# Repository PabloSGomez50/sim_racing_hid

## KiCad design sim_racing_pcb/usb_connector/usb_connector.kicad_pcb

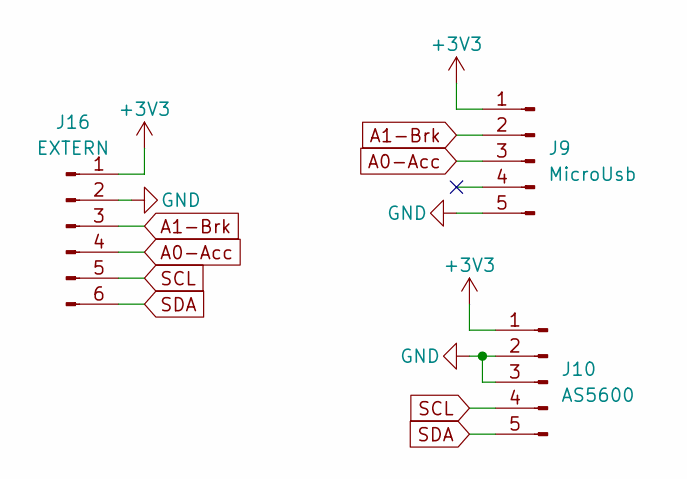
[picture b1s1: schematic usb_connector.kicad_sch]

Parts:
J9: MicroUsb; PinHeader_1x05_P2.54mm_Vertical
J10: AS5600; PinHeader_1x05_P2.54mm_Vertical
J16: EXTERN; Molex_KK-254_AE-6410-06A_1x06_P2.54mm_Vertical

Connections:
+3V3: J9.1, J10.1, J16.1
A0-Acc: J9.3, J16.4
A1-Brk: J9.2, J16.3
GND: J9.5, J10.2, J10.3, J16.2
SCL: J10.4, J16.5
SDA: J10.5, J16.6

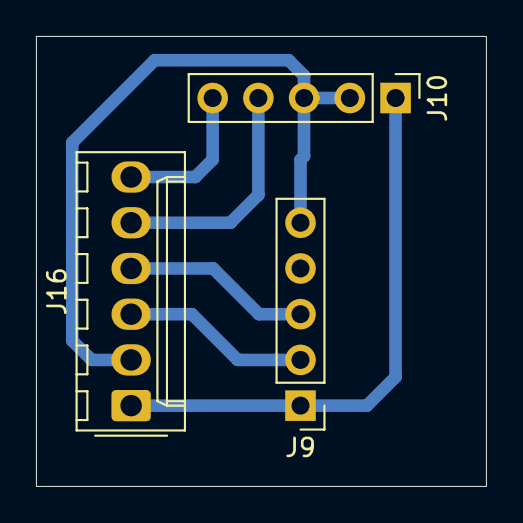
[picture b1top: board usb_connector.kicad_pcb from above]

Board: 2 copper layers, 25.0 x 25.0 mm, 3 parts (0 on the bottom side), 6 nets.

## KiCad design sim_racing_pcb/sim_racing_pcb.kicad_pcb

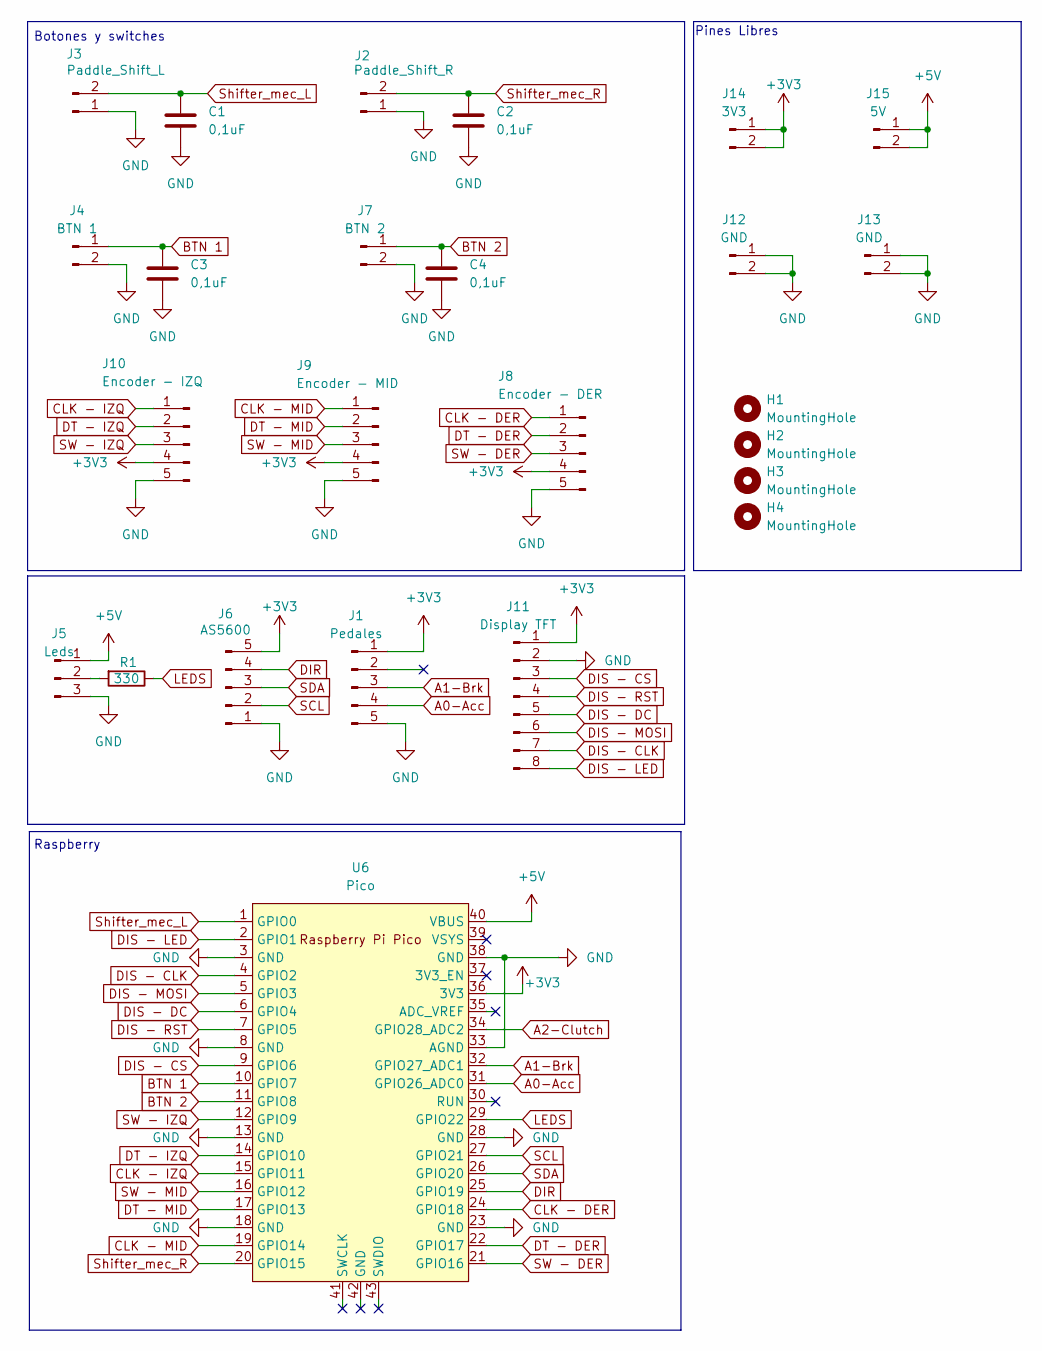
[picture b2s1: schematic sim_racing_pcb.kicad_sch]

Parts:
C1, C2, C3, C4: 0,1uF; C_Disc_D3.4mm_W2.1mm_P2.50mm
H1, H2, H3, H4: MountingHole; MountingHole_3.2mm_M3_DIN965
J1: Pedales; Molex_KK-254_AE-6410-05A_1x05_P2.54mm_Vertical
J2: Paddle_Shift_R; Molex_KK-254_AE-6410-02A_1x02_P2.54mm_Vertical
J3: Paddle_Shift_L; Molex_KK-254_AE-6410-02A_1x02_P2.54mm_Vertical
J4: BTN 1; Molex_KK-254_AE-6410-02A_1x02_P2.54mm_Vertical
J5: Leds; Molex_KK-254_AE-6410-03A_1x03_P2.54mm_Vertical
J6: AS5600; Molex_KK-254_AE-6410-05A_1x05_P2.54mm_Vertical
J7: BTN 2; Molex_KK-254_AE-6410-02A_1x02_P2.54mm_Vertical
J8: Encoder - DER; Molex_KK-254_AE-6410-05A_1x05_P2.54mm_Vertical
J9: Encoder - MID; Molex_KK-254_AE-6410-05A_1x05_P2.54mm_Vertical
J10: Encoder - IZQ; Molex_KK-254_AE-6410-05A_1x05_P2.54mm_Vertical
J11: Display TFT; Molex_KK-254_AE-6410-08A_1x08_P2.54mm_Vertical
J12, J13: GND; PinHeader_1x02_P2.54mm_Vertical
J14: 3V3; PinHeader_1x02_P2.54mm_Vertical
J15: 5V; PinHeader_1x02_P2.54mm_Vertical
R1: 330; R_Axial_DIN0207_L6.3mm_D2.5mm_P15.24mm_Horizontal
U6: Pico; RPi_Pico_SMD_TH

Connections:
+3V3: J1.1, J6.5, J8.4, J9.4, J10.4, J11.1, J14.1, J14.2, U6.36 (3V3); also elsewhere on the board
+5V: J5.1, J15.1, J15.2, U6.40 (VBUS)
A0-Acc: J1.4, U6.31 (GPIO26_ADC0); also elsewhere on the board
A1-Brk: J1.3, U6.32 (GPIO27_ADC1); also elsewhere on the board
A2-Clutch: U6.34 (GPIO28_ADC2)
BTN 1: C3.1, J4.1, U6.10 (GPIO7)
BTN 2: C4.1, J7.1, U6.11 (GPIO8)
CLK - DER: J8.1, U6.24 (GPIO18)
CLK - IZQ: J10.1, U6.15 (GPIO11)
CLK - MID: J9.1, U6.19 (GPIO14)
DIS - CLK: J11.7, U6.4 (GPIO2)
DIS - CS: J11.3, U6.9 (GPIO6)
DIS - DC: J11.5, U6.6 (GPIO4)
DIS - LED: J11.8, U6.2 (GPIO1)
DIS - MOSI: J11.6, U6.5 (GPIO3)
DIS - RST: J11.4, U6.7 (GPIO5)
DT - DER: J8.2, U6.22 (GPIO17)
DT - IZQ: J10.2, U6.14 (GPIO10)
DT - MID: J9.2, U6.17 (GPIO13)
LEDS: R1.1, U6.29 (GPIO22)
unnamed: J5.2, R1.2
SCL: J6.2, U6.27 (GPIO21); also elsewhere on the board
SDA: J6.3, U6.26 (GPIO20); also elsewhere on the board
SW - DER: J8.3, U6.21 (GPIO16)
SW - IZQ: J10.3, U6.12 (GPIO9)
SW - MID: J9.3, U6.16 (GPIO12)
Shifter_mec_L: C1.1, J3.2, U6.1 (GPIO0)
Shifter_mec_R: C2.1, J2.2, U6.20 (GPIO15)

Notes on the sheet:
Botones y switches
Pines Libres
Raspberry

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
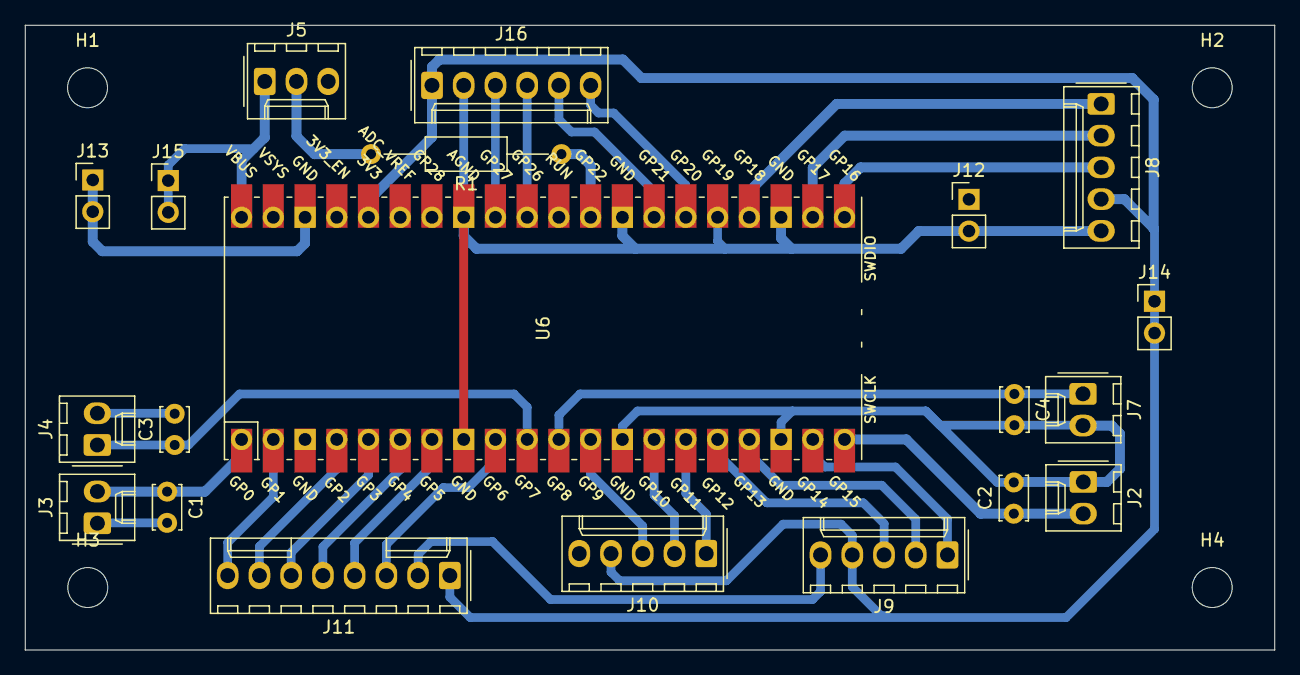
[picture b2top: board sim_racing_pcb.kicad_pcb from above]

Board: 2 copper layers, 100.0 x 50.0 mm, 24 parts (0 on the bottom side), 28 nets.

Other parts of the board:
J16: EXTERN; Molex_KK-254_AE-6410-06A_1x06_P2.54mm_Vertical

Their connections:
+3V3: J16.1; also elsewhere on the board
A0-Acc: J16.4; also elsewhere on the board
A1-Brk: J16.3; also elsewhere on the board
SCL: J16.5; also elsewhere on the board
SDA: J16.6; also elsewhere on the board

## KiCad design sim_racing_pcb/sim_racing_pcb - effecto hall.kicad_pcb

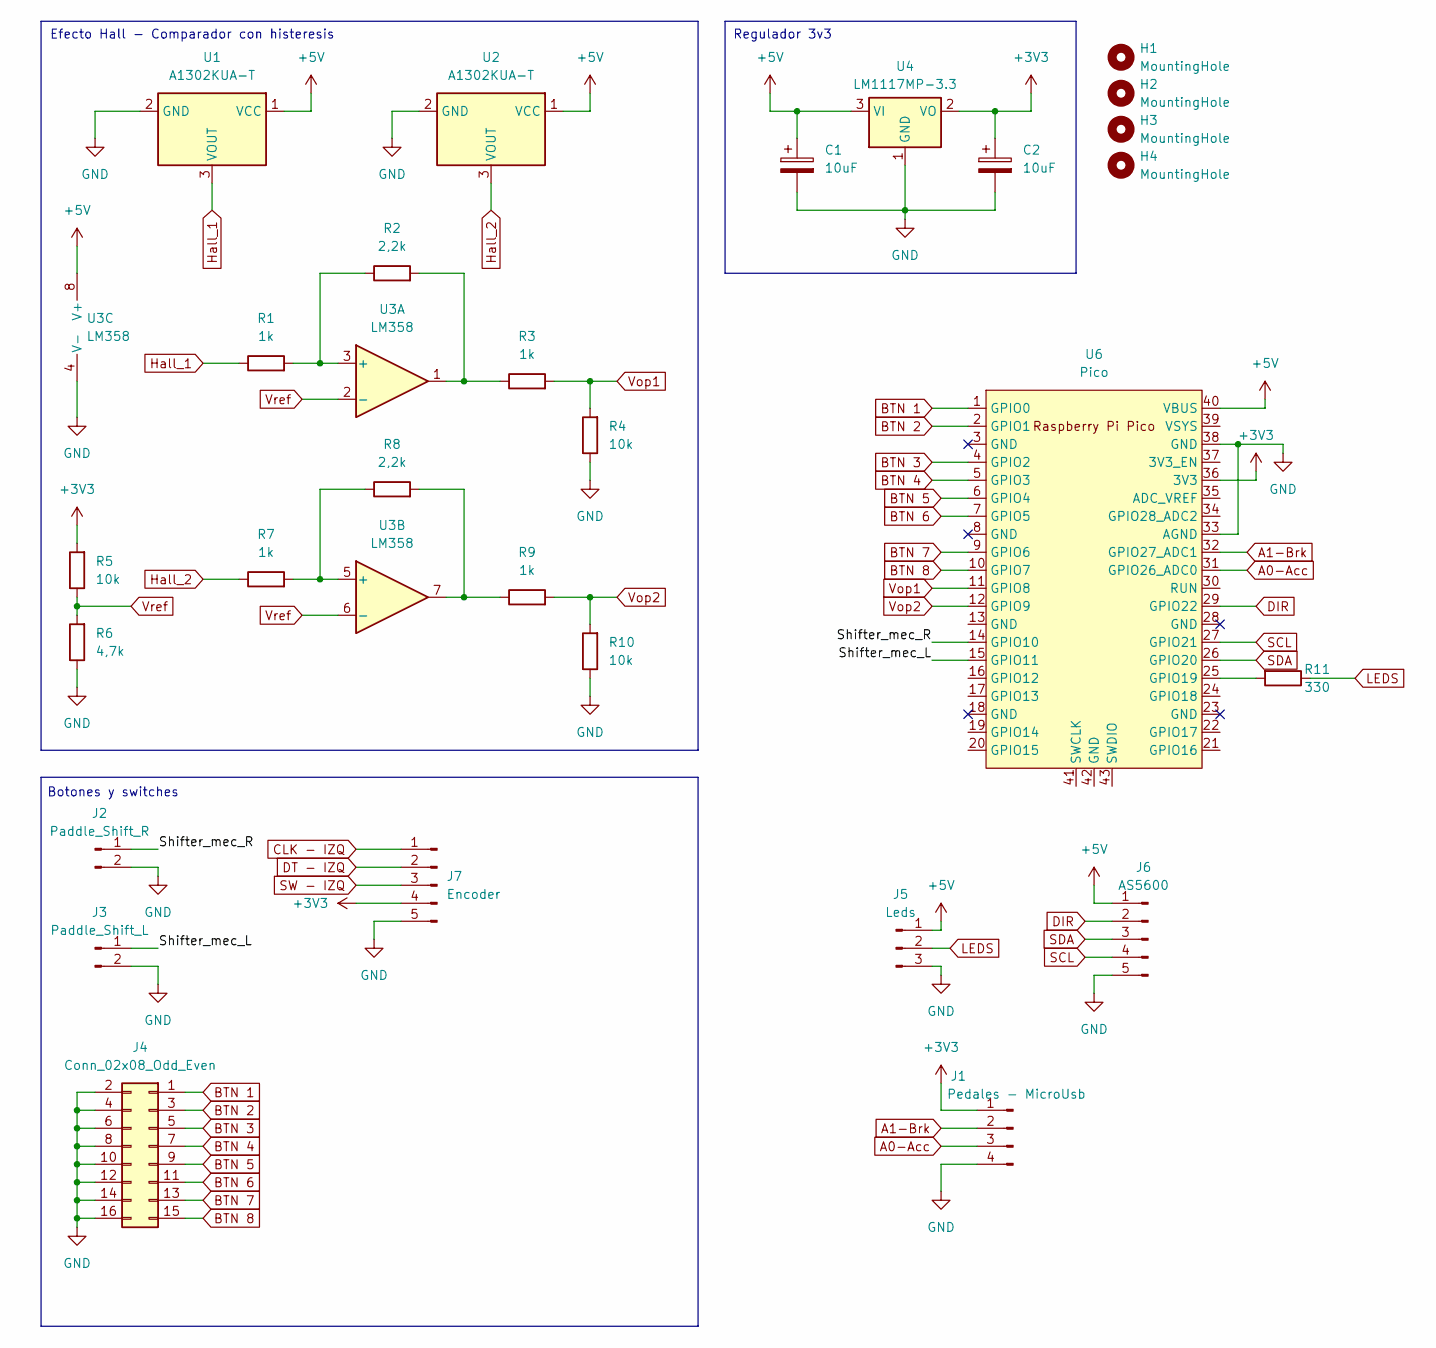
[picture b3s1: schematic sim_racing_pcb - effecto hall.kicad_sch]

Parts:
C1, C2: 10uF; CP_Radial_D5.0mm_P2.50mm
H1, H2, H3, H4: MountingHole; MountingHole_3.2mm_M3_DIN965
J1: Pedales - MicroUsb; PinHeader_1x04_P2.54mm_Vertical
J2: Paddle_Shift_R; PinHeader_1x02_P2.54mm_Vertical
J3: Paddle_Shift_L; PinHeader_1x02_P2.54mm_Vertical
J4: Conn_02x08_Odd_Even; PinHeader_2x08_P2.54mm_Vertical
J5: Leds; PinHeader_1x03_P2.54mm_Vertical
J6: AS5600; PinHeader_1x05_P2.54mm_Vertical
J7: Encoder; PinHeader_1x05_P2.54mm_Vertical
R1, R3, R7, R9: 1k; R_Axial_DIN0207_L6.3mm_D2.5mm_P10.16mm_Horizontal
R2, R8: 2,2k; R_Axial_DIN0207_L6.3mm_D2.5mm_P10.16mm_Horizontal
R4, R5, R10: 10k; R_Axial_DIN0207_L6.3mm_D2.5mm_P10.16mm_Horizontal
R6: 4,7k; R_Axial_DIN0207_L6.3mm_D2.5mm_P10.16mm_Horizontal
R11: 330; R_Axial_DIN0207_L6.3mm_D2.5mm_P10.16mm_Horizontal
U1, U2: A1302KUA-T; PinHeader_1x03_P2.54mm_Vertical
U3: LM358; DIP-8_W10.16mm_LongPads
U4: LM1117MP-3.3; SOT-223-3_TabPin2
U6: Pico; RPi_Pico_SMD_TH

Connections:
+3V3: C2.1, J1.1, J7.4, R5.2, U4.2 (VO), U6.36 (3V3)
+5V: C1.1, J5.1, J6.1, U1.1 (VCC), U2.1 (VCC), U3.8 (V+), U4.3 (VI), U6.40 (VBUS)
/Shifter_mec_L: J3.1, U6.15 (GPIO11)
/Shifter_mec_R: J2.1, U6.14 (GPIO10)
A0-Acc: J1.3, U6.31 (GPIO26_ADC0)
A1-Brk: J1.2, U6.32 (GPIO27_ADC1)
BTN 1: J4.1, U6.1 (GPIO0)
BTN 2: J4.3, U6.2 (GPIO1)
BTN 3: J4.5, U6.4 (GPIO2)
BTN 4: J4.7, U6.5 (GPIO3)
BTN 5: J4.9, U6.6 (GPIO4)
BTN 6: J4.11, U6.7 (GPIO5)
BTN 7: J4.13, U6.9 (GPIO6)
BTN 8: J4.15, U6.10 (GPIO7)
DIR: J6.2, U6.29 (GPIO22)
GND: C1.2, C2.2, J1.4, J2.2, J3.2, J4.2, J4.4, J4.6, J4.8, J4.10, J4.12, J4.14, J4.16, J5.3, J6.5, J7.5, R4.1, R6.1, R10.1, U1.2 (GND), U2.2 (GND), U3.4 (V-), U4.1 (GND), U6.33 (AGND), U6.38 (GND)
Hall_1: R1.1, U1.3 (VOUT)
Hall_2: R7.1, U2.3 (VOUT)
LEDS - Neopixel: J5.2, R11.1, R11.2, U6.25 (GPIO19)
unnamed: R2.2, R3.1, U3.1
unnamed: R8.2, R9.1, U3.7
unnamed: R1.2, R2.1, U3.3 (+)
unnamed: R7.2, R8.1, U3.5 (+)
SCL: J6.4, U6.27 (GPIO21)
SDA: J6.3, U6.26 (GPIO20)
Vop1: R3.2, R4.2, U6.11 (GPIO8)
Vop2: R9.2, R10.2, U6.12 (GPIO9)
Vref: R5.1, R6.2, U3.2 (-), U3.6 (-)

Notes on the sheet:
Botones y switches
Regulador 3v3
Efecto Hall - Comparador con histeresis

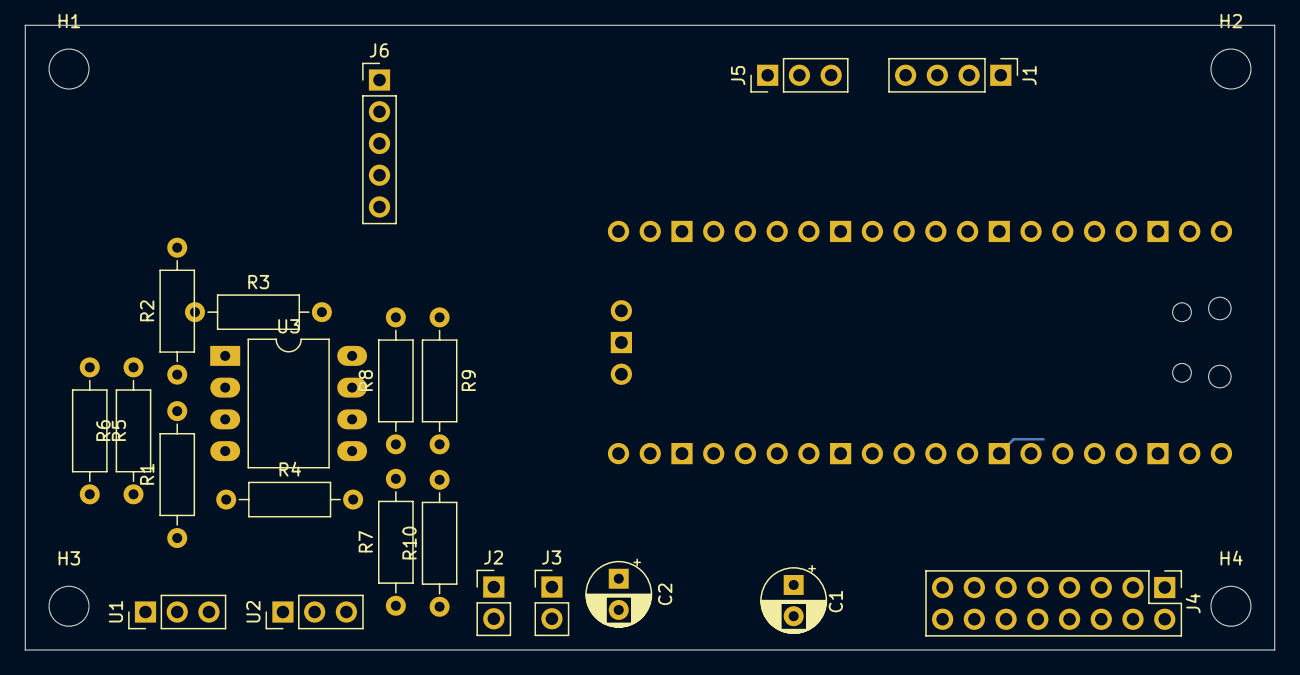
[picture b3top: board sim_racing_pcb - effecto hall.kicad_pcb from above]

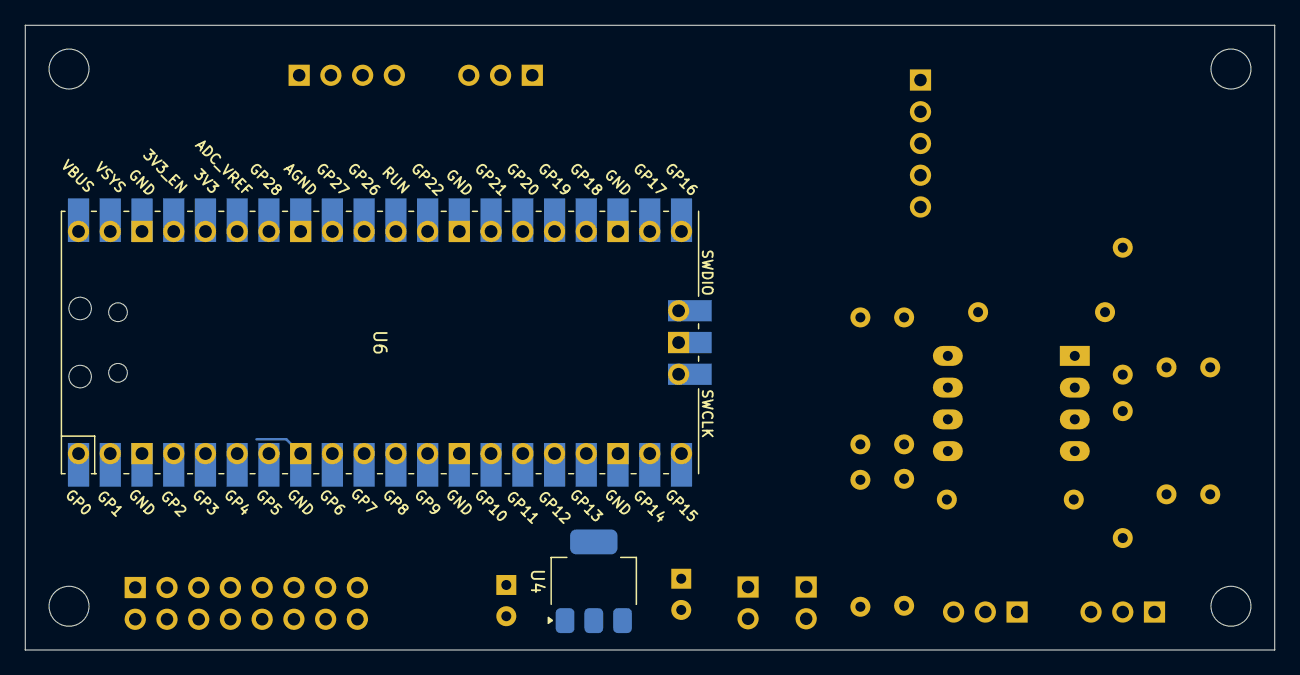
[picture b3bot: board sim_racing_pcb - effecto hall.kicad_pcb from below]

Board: 2 copper layers, 100.0 x 50.0 mm, 27 parts (2 on the bottom side), 28 nets.

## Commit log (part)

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2024-08-15 feat: read values from ADC and as5600. Error in HID descriptor
2024-08-22 Add z axis and Hat switch to descriptor
2024-10-10 Add: default pcb
2024-10-10 small change in setz and disable x and y
2024-10-12 feat: v1 volante y pedalera
    Rutina de calibracion pedales
2025-03-22 codigo de relleno usb lib en C
2025-03-31 Ordenar archivos y primera prueba con hid usb en C
2025-04-23 remove incorrect build files in rpico2
2025-04-29 Python HID monitor
2025-04-29 version estable de hid con rpico2
2025-07-19 add task_functions
2025-07-22 minor changes to pcb
2025-07-24 update display.py in circuitPython code
2025-07-24 rename firmware for c code
2025-07-24 modify pcb display placement
2025-07-24 remove pico-extras
2025-07-25 add lvgl and working version
2025-07-25 working test of as5600
2025-07-25 Remove power selection for as5600 and change for molex connectors
2025-07-25 modify position of buttons
2025-07-25 add as5600 test baremetal
2025-07-25 add btns test baremetal
2025-07-25 add ws2812 leds baremetal
2025-07-27 update functions in test libs
2025-07-27 add libs to main project
2025-07-27 Modify usb and as5600 connectors for unique 6 cable molex
2025-08-01 add_usb_connector
2025-10-08 fix: as5600 read
2025-10-08 chore: test tft
2026-04-11 chore: adjust pins
2026-04-11 feat: first communication using UDP
2026-04-13 chore: ili9341 and lvgl integration
2026-04-13 chore: move buttons outside main and create encoders
2026-04-14 chore: first test of HID PID standard. Data receive from python not F1 2020 game
2026-04-20 chore: first F1 2020 PID communication, no Force report
2026-05-10 chore: add adc in pico hid pid
